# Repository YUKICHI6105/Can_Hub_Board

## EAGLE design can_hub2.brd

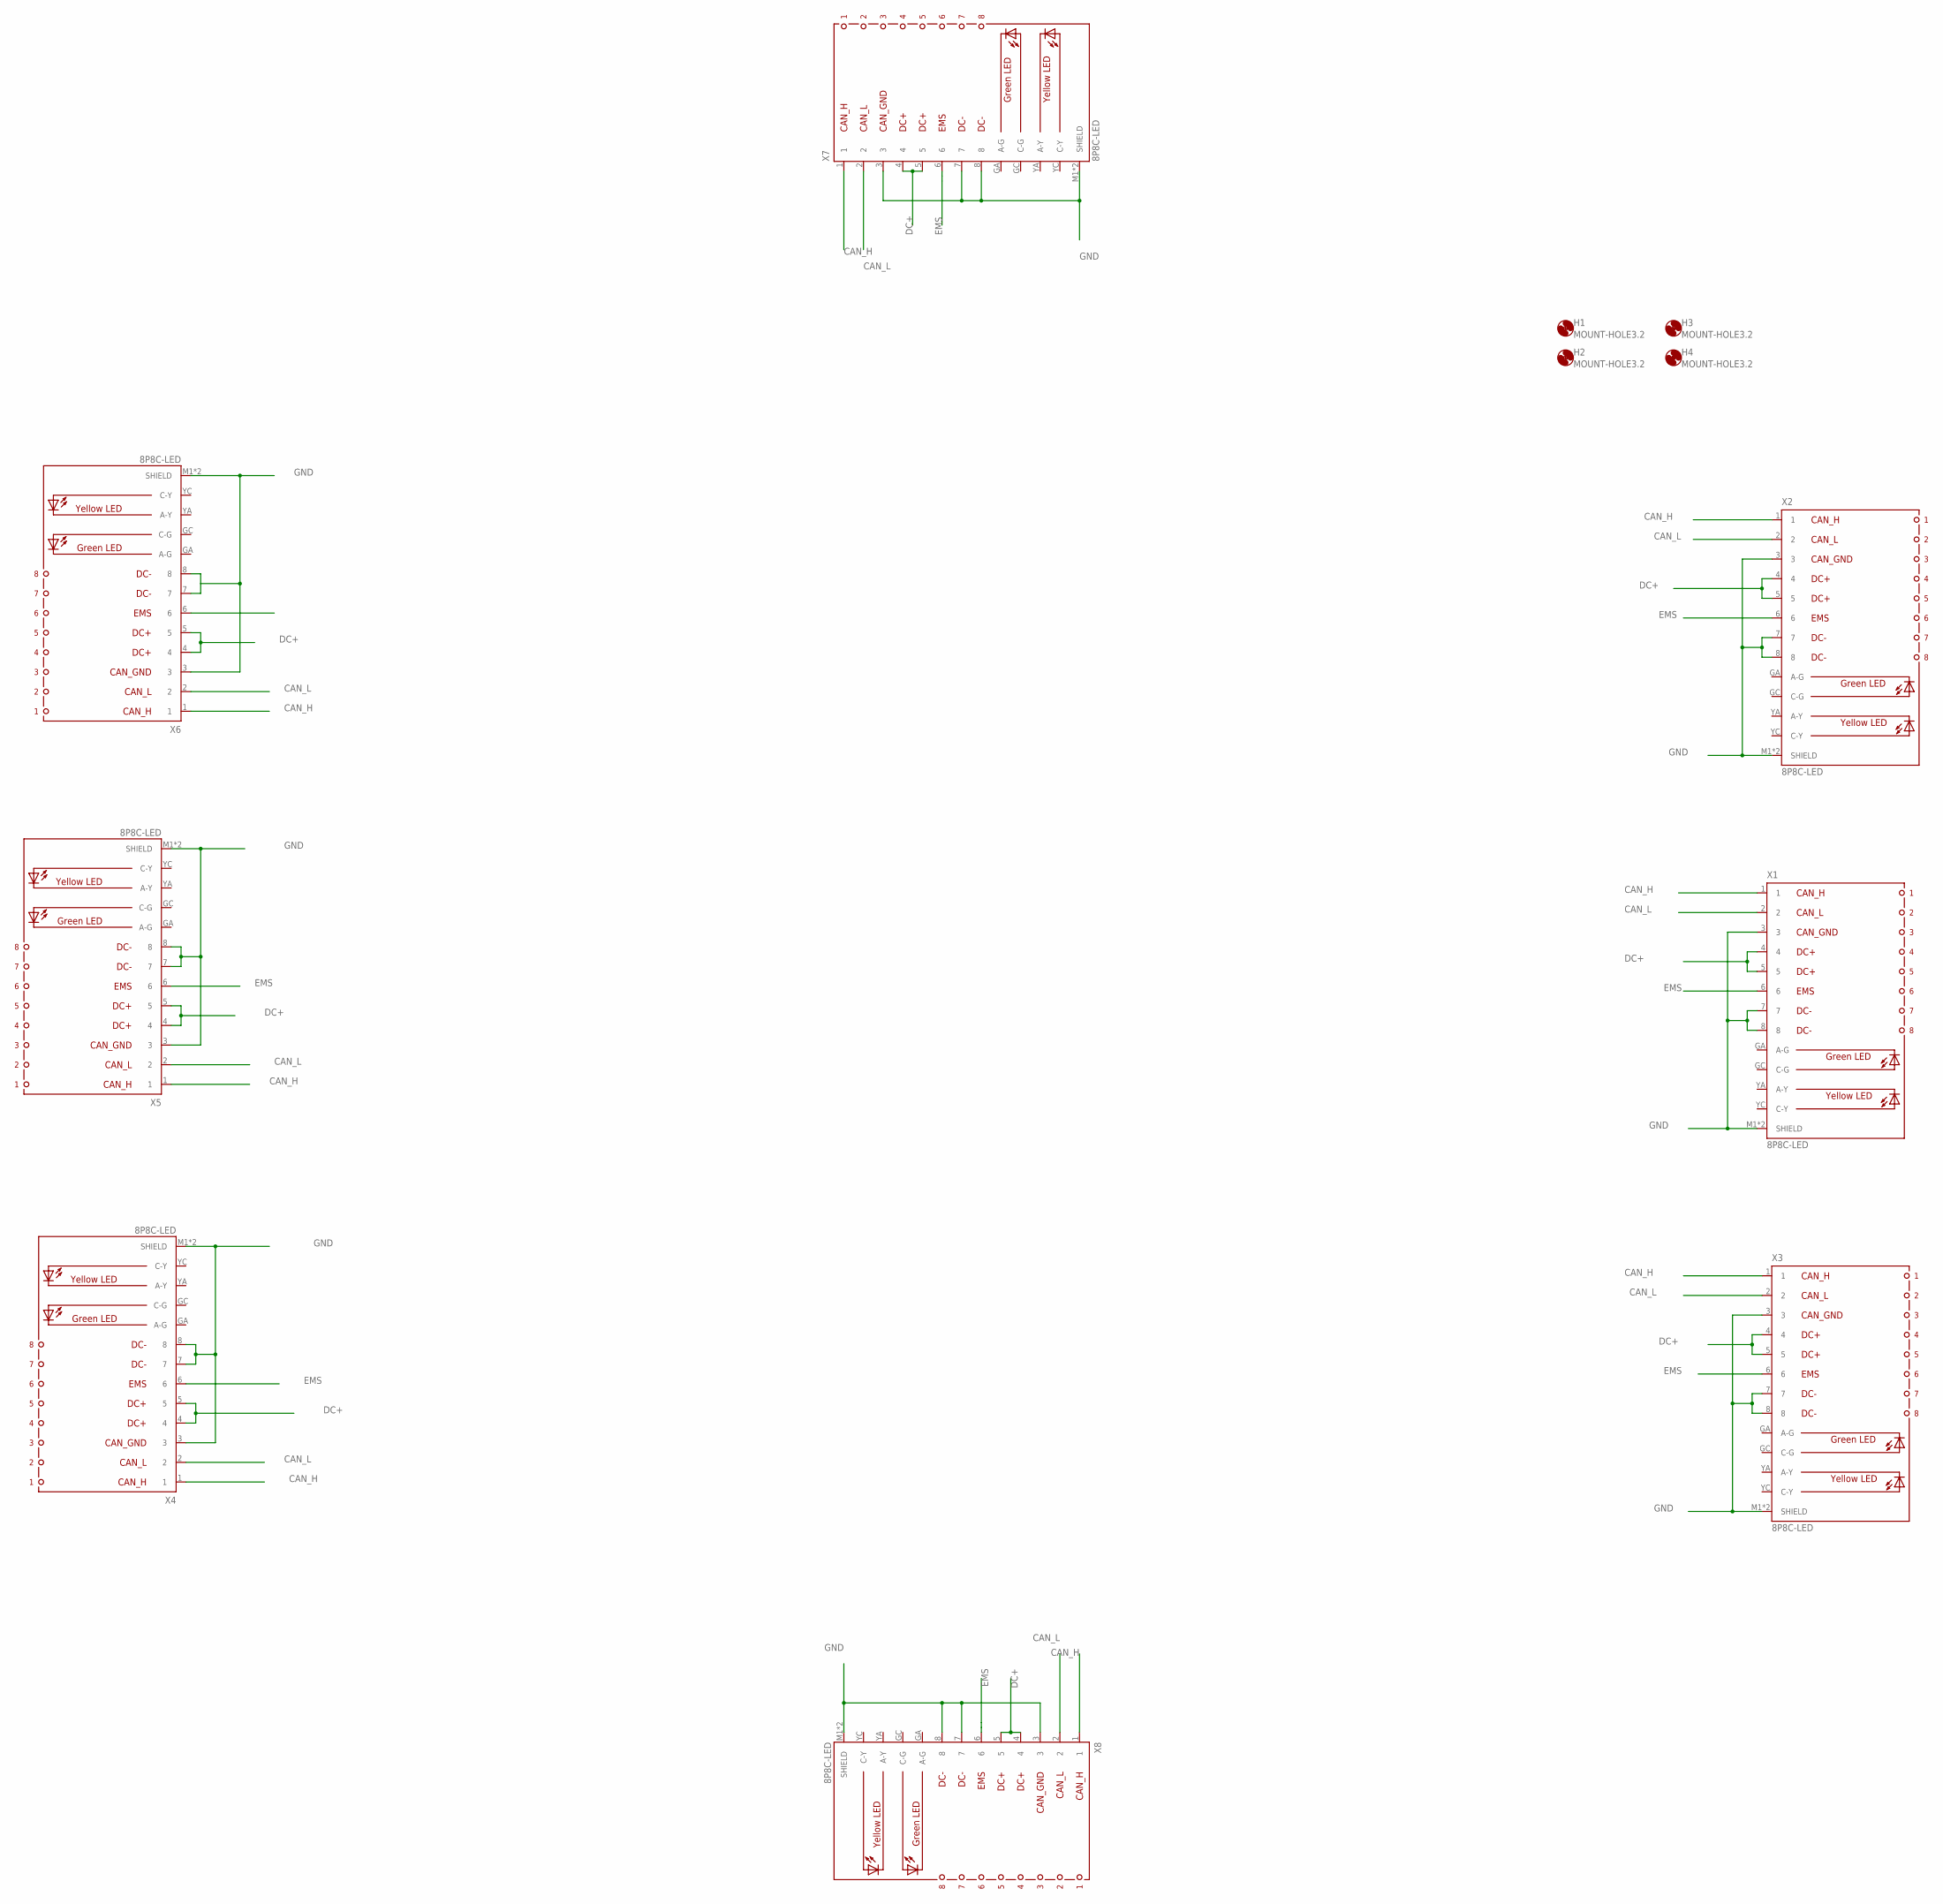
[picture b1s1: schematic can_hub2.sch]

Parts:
H1, H2, H3, H4: MOUNT-HOLE3.2; 3,2
X1, X2, X3, X4, X5, X6, X7, X8: 8P8C-LED

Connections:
CAN_H: X1.1, X2.1, X3.1, X4.1, X5.1, X6.1, X7.1, X8.1
CAN_L: X1.2, X2.2, X3.2, X4.2, X5.2, X6.2, X7.2, X8.2
DC+: X1.4, X1.5, X2.4, X2.5, X3.4, X3.5, X4.4, X4.5, X5.4, X5.5, X6.4, X6.5, X7.4, X7.5, X8.4, X8.5
EMS: X1.6, X2.6, X3.6, X4.6, X5.6, X6.6, X7.6, X8.6
GND: X1.3, X1.7, X1.8, X1.M1 (SHIELD), X1.M2 (SHIELD), X2.3, X2.7, X2.8, X2.M1 (SHIELD), X2.M2 (SHIELD), X3.3, X3.7, X3.8, X3.M1 (SHIELD), X3.M2 (SHIELD), X4.3, X4.7, X4.8, X4.M1 (SHIELD), X4.M2 (SHIELD), X5.3, X5.7, X5.8, X5.M1 (SHIELD), X5.M2 (SHIELD), X6.3, X6.7, X6.8, X6.M1 (SHIELD), X6.M2 (SHIELD), X7.3, X7.7, X7.8, X7.M1 (SHIELD), X7.M2 (SHIELD), X8.3, X8.7, X8.8, X8.M1 (SHIELD), X8.M2 (SHIELD)

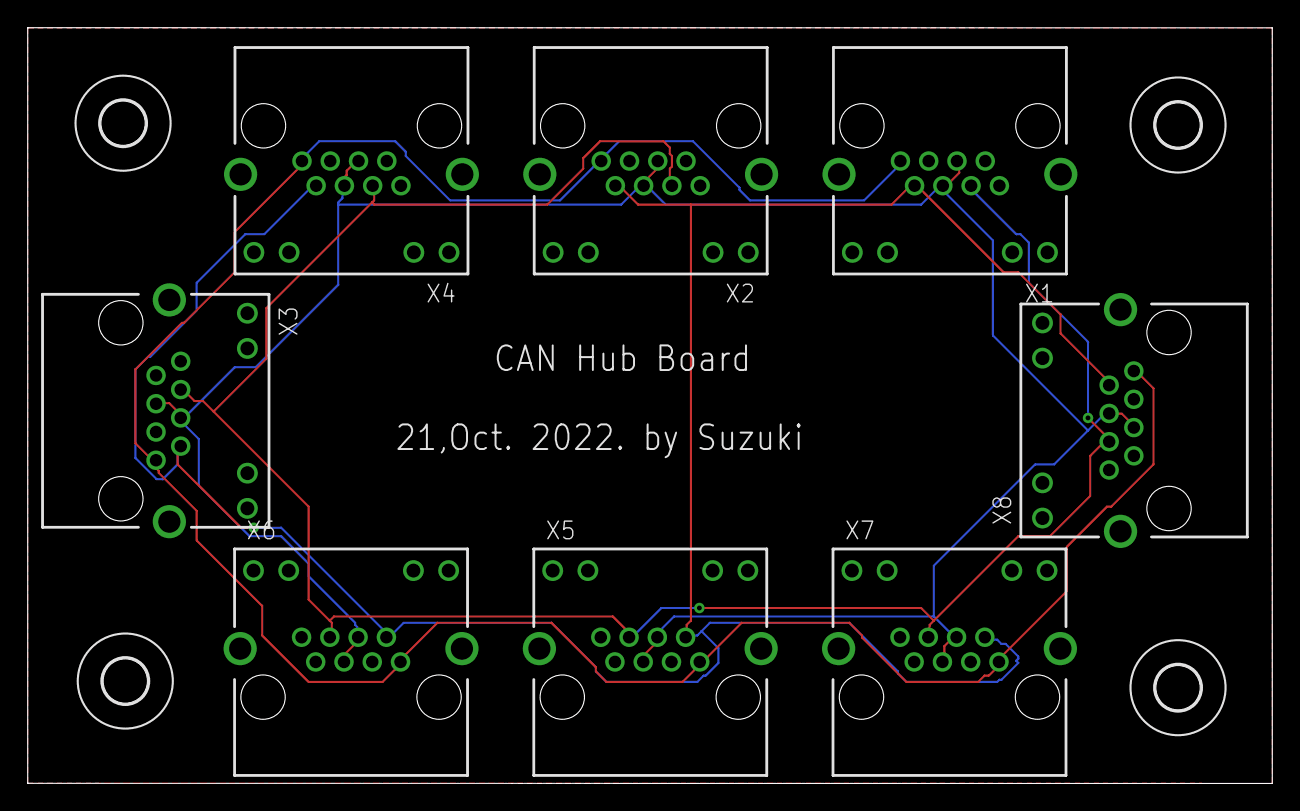
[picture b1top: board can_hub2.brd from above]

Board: 2 copper layers, 89.8 x 54.5 mm, 12 parts (0 on the bottom side), 5 nets.
